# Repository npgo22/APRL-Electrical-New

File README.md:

# APRL KiCad Projects

APRL KiCad Projects.

## Setup
First, clone the repository with `git clone`. GitHub has a button which gives you the command to do this.
Then, you will have to use `git lfs pull` to get all the 3D models and images.

To use the board templates, set `KICAD_USER_TEMPLATE_DIR` by:

1. Going to Preferences > Configure Paths...
2. Setting `KICAD_USER_TEMPLATE_DIR` to wherever you cloned this repo + `/kicadlibs/templates`

## New ALI (Current Project for FQ2026)

### Design
The exigence of this endeavour is twofold:
1. To test the analog frontend designs of our proposed boards for DPF
2. To replace the confusing and elaborate ALI electronics with something that is far better documented and easier to use

The ALI itself can continue to be used for years to come and this reworking of the electronics will not impact it at all. This is going to be its own separate electrical box altogether. The ALI has the following additional limitations, too:
1. Limited I/O
2. Bonded grounds between +24/12/5V power supplies
3. Unknown board-level design decisions/trade-offs made in off-the-shelf components leading to strange artifacts in various measurements
4. Is generally really difficult to understand
5. Mixes bodge-wired custom electronics, off-the-shelf parts, and protoboards
6. Generally has fairly poor mounting
7. Makes use of fairly terrible connectors which are partially damaged and/or have shields which are not properly tied to case GND
8. Is completely full, thus making it impossible to add more electronics
9. Has no methods of cooling, sans the empty hold in the side of the box which completely negate the weather rating of the box itself
10. Uses heterogenous embedded computing ecosystems, requiring cross-domain knowledge of embassy, STM32Cube, and Arduino while doing every single one of them somewhat wrong in one way or another
11. Lacks feedback in many places (error logging namely)
12. Is generally just really hard to work with

Therefore, we have started work on a true replacement. Each of the modules serve a specific task, and are hooked to a common ethernet-based network which is far more performant than the original layout while simultaneously being easier to understand and expand. If you want more I/O, you can just simply add another board within a few minutes. Likewise, by opting for cutouts in the enclosure over dedicated port holes, it is also far easier to revise significant parts of the design without needing to drill through steel. 

#### Power
This system is +5V and +24V only, with +3.3V regulated on each board.

### CANBUS vs Ethernet
On the ground station, we are planning to use Ethernet instead of CANBUS. While this means our session protocol will not be tested in a real-world hotfire scenario, it does mean we can fully exploit each of the features offered by ethernet:
- Higher bandwidth (upwards of ~50x) means we don't have to throttle anything including error logging
- Natural isolation means we don't need any special tricks to get grounded thermocouples to work
- Is just generally far more pleasant to work with
- Does not limit future design decisions should we decide to reuse anything

Each of the modules will have a CAN transceiver anyway available for testing.

## Repository layout

```
kicadlibs/                                 Shared KiCad libraries
  aprl/                                      APRL's custom symbols and footprints
  aprl/*-noct.pretty                         "aprl/" but without courtyards
  vendor/                                    Third-party libs
  models/                                    3D models KiCad does not ship
  APRL_*_Sheet.kicad_wks                     Drawing sheets
  jlcpcb-4layer.kicad_dru                    Canonical JLCPCB design rules
.github/scripts                              Helper scripts runnable via Just and GH actions

ali/2/                                     New ALI electronics
ali/1/                                     Old ALI electronics
ophio/                                     DPF Vehicle Boards
misc/                                      Other endeavors
```

## What's not in this repo
- Old code (incl thermocouple 1A's CubeMX and Embassy variants)
- Prototypes (pending ordering)
- ALI ADC hardware (pending import)

## AI Usage
You may use AI to research topics and to write one-off scripts which do minor modifications and automate tedious, minor tasks. For example, if you need to color in a bunch of models feel free to.

What you *cannot* use it for is end to end electrical design, layout, and documentation. Documents should be written by people, and a schematic falls under this category. Likewise, using AI to automate layout is A. ineffective because it does not generate high-quality layouts and B. defeats the purpose of this club, which is to learn about electronics.

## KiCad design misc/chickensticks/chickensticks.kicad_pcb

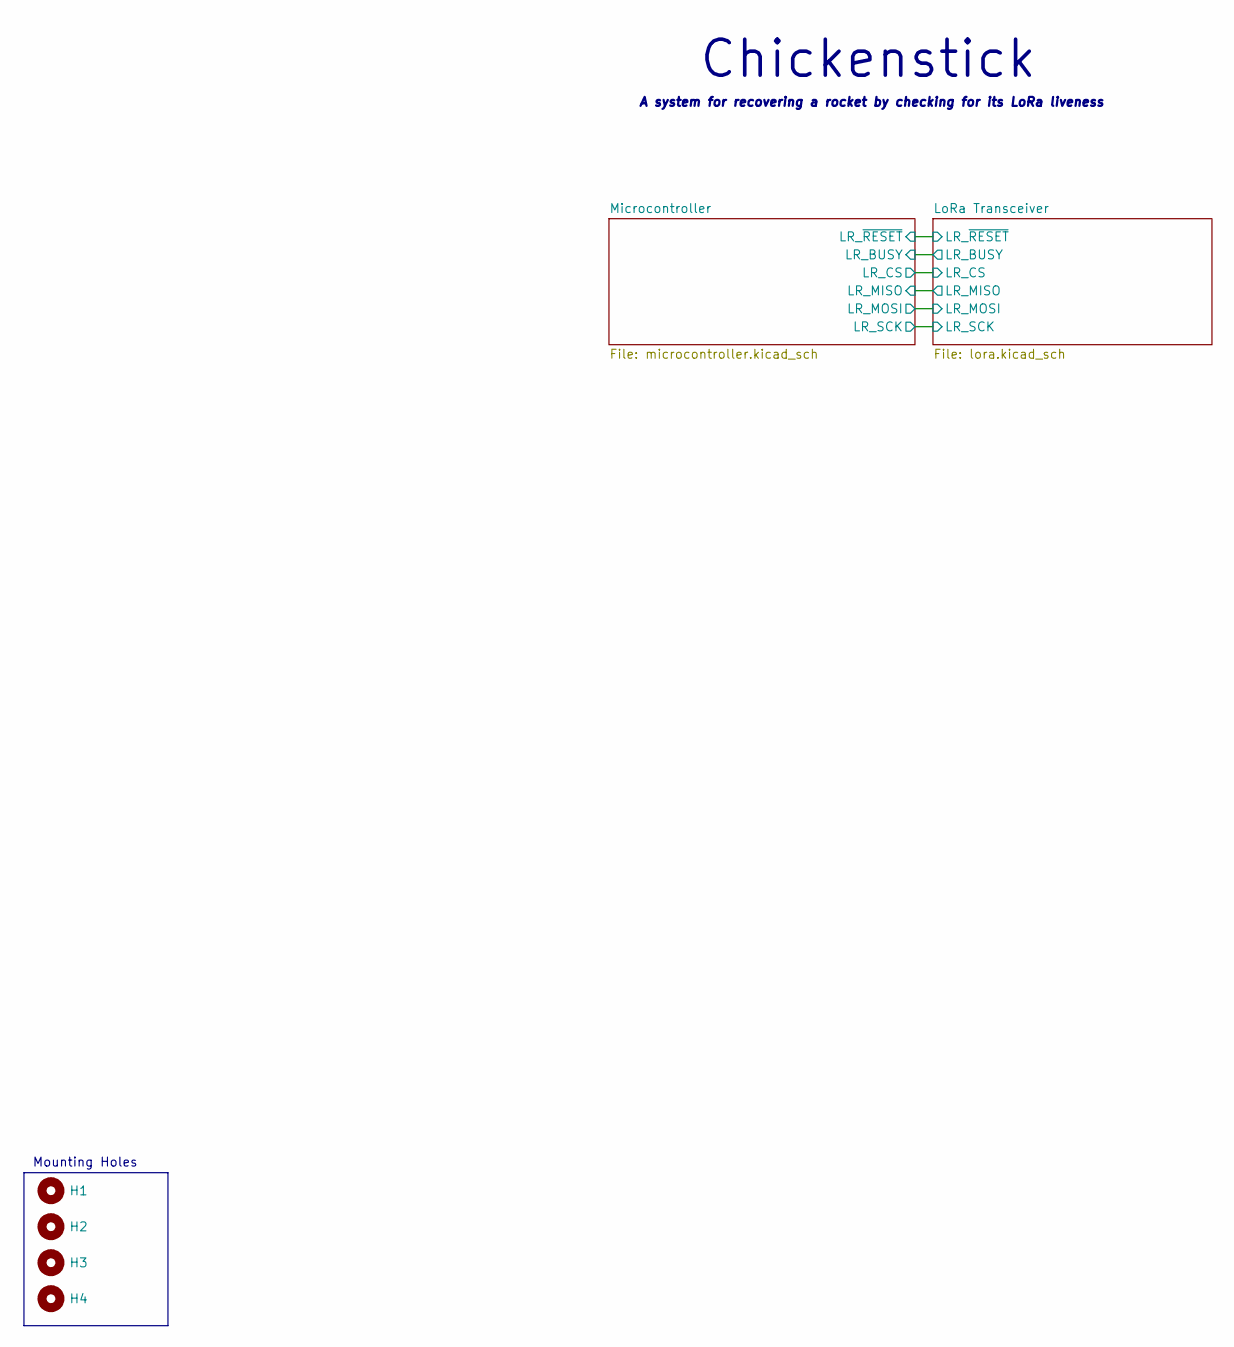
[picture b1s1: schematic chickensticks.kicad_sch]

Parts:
H1, H2, H3, H4: MountingHole; MountingHole_3.2mm_M3

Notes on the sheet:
Chickenstick
A system for recovering a rocket by checking for its LoRa liveness
Mounting Holes

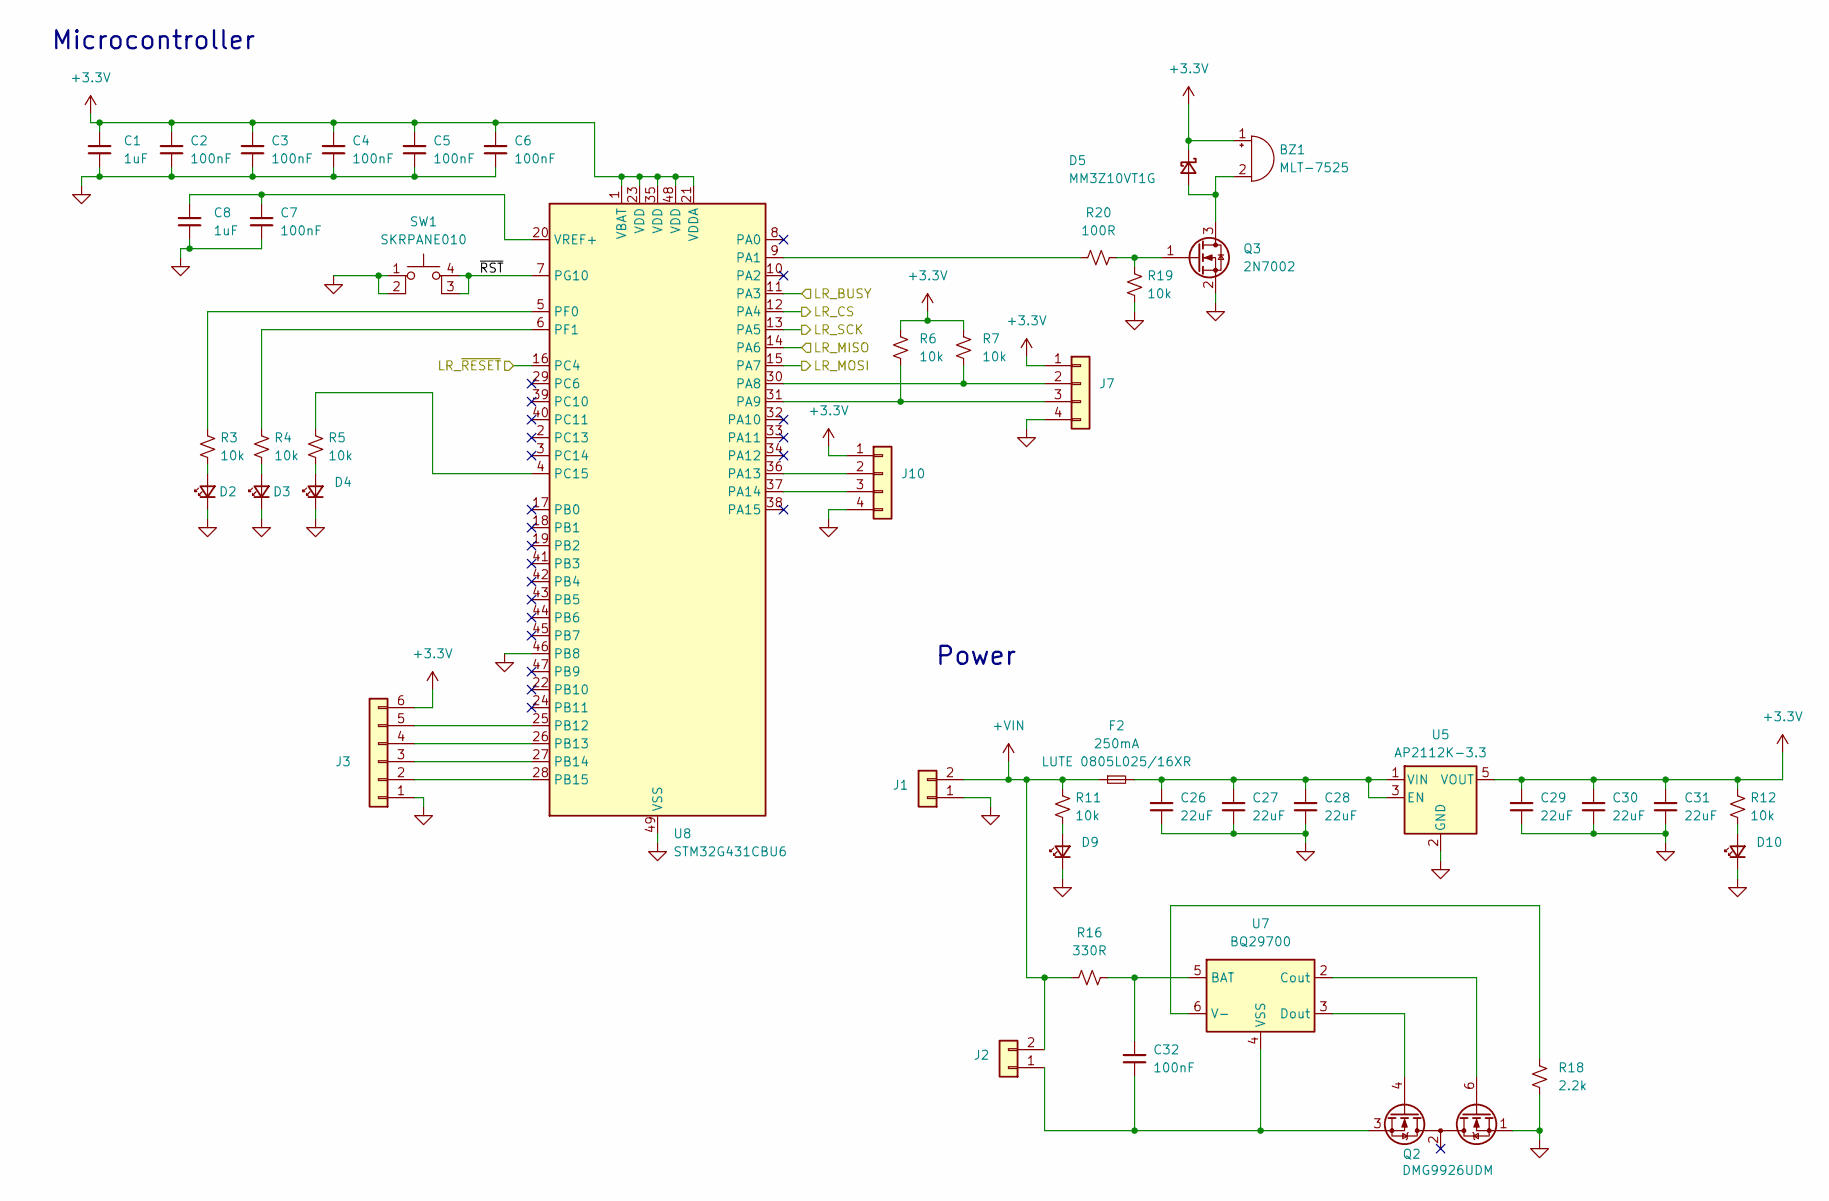
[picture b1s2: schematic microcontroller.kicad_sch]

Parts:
BZ1: MLT-7525
C1, C8: 1uF; C_0805
C2, C3, C4, C5, C6, C7, C32: 100nF; C_0603
C26, C27, C28, C29, C30, C31: 22uF; C_0805
D2, D3, D4, D9, D10: LED_Small; LED_0603
D5: MM3Z10VT1G; SOD-323
F2: 250mA; Fuse_0805_2012Metric
J1, J2: Conn_01x02; Molex_KK-254_AE-6410-02A_1x02_P2.54mm_Vertical
J3: Conn_01x06; Molex_KK-254_AE-6410-06A_1x06_P2.54mm_Vertical
J7, J10: Conn_01x04; PinHeader_1x04_P2.54mm_Vertical
Q2: DMG9926UDM; SOT-23-6
Q3: 2N7002; SOT-23
R3, R4, R5, R6, R7, R11, R12, R19: 10k; R_0603
R16: 330R; R_0603
R18: 2.2k; R_0603
R20: 100R; R_0603
SW1: SKRPANE010
U5: AP2112K-3.3; SOT-23-5
U7: BQ29700; WSON-6_1.5x1.5mm_P0.5mm
U8: STM32G431CBU6; QFN-48_EP_7.3x7.3_Pitch0.5mm

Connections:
+3.3V: BZ1.1 (+), C1.1, C2.1, C3.1, C4.1, C5.1, C6.1, C29.1, C30.1, C31.1, D5.1 (K), J3.6, J7.1, J10.1, R6.1, R7.1, R12.1, U5.5 (VOUT), U8.1 (VBAT), U8.21 (VDDA), U8.23 (VDD), U8.35 (VDD), U8.48 (VDD); also elsewhere on the board
+VIN: F2.1, J1.2, J2.2, R11.1, R16.1
/LoRa Transceiver/LR_BUSY: U8.11 (PA3); also elsewhere on the board
/LoRa Transceiver/LR_CS: U8.12 (PA4); also elsewhere on the board
/LoRa Transceiver/LR_MISO: U8.14 (PA6); also elsewhere on the board
/LoRa Transceiver/LR_MOSI: U8.15 (PA7); also elsewhere on the board
/LoRa Transceiver/LR_SCK: U8.13 (PA5); also elsewhere on the board
/LoRa Transceiver/LR_~RESET: U8.16 (PC4); also elsewhere on the board
/Microcontroller/~RST: SW1.3 (K), SW1.4 (A), U8.7 (PG10)
GND: C1.2, C2.2, C3.2, C4.2, C5.2, C6.2, C7.2, C8.2, C26.2, C27.2, C28.2, C29.2, C30.2, C31.2, D2.1 (K), D3.1 (K), D4.1 (K), D9.1 (K), D10.1 (K), J1.1, J3.1, J7.4, J10.4, Q2.1 (D1), Q3.2 (S), R18.2, R19.2, SW1.1, SW1.2, U5.2 (GND), U8.46 (PB8), U8.49 (VSS); also elsewhere on the board
unnamed: BZ1.2 (-), D5.2 (A), Q3.3 (D)
unnamed: D2.2 (A), R3.2
unnamed: D3.2 (A), R4.2
unnamed: D4.2 (A), R5.2
unnamed: D9.2 (A), R11.2
unnamed: D10.2 (A), R12.2
unnamed: C32.2, J2.1, Q2.3 (S2), U7.4 (VSS)
unnamed: J3.2, U8.28 (PB15)
unnamed: J3.3, U8.27 (PB14)
unnamed: J3.4, U8.26 (PB13)
unnamed: J3.5, U8.25 (PB12)
unnamed: J7.2, R7.2, U8.30 (PA8)
unnamed: J7.3, R6.2, U8.31 (PA9)
unnamed: J10.2, U8.36 (PA13)
unnamed: J10.3, U8.37 (PA14)
unnamed: Q2.6 (G1), U7.2 (Cout)
unnamed: Q2.4 (G2), U7.3 (Dout)
unnamed: Q3.1 (G), R19.1, R20.2
unnamed: C26.1, C27.1, C28.1, F2.2, U5.1 (VIN), U5.3 (EN)
unnamed: C32.1, R16.2, U7.5 (BAT)
unnamed: R18.1, U7.6 (V-)
unnamed: R20.1, U8.9 (PA1)
unnamed: R5.1, U8.4 (PC15)
unnamed: R3.1, U8.5 (PF0)
unnamed: R4.1, U8.6 (PF1)
unnamed: C7.1, C8.1, U8.20 (VREF+)

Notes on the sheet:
Microcontroller
Power

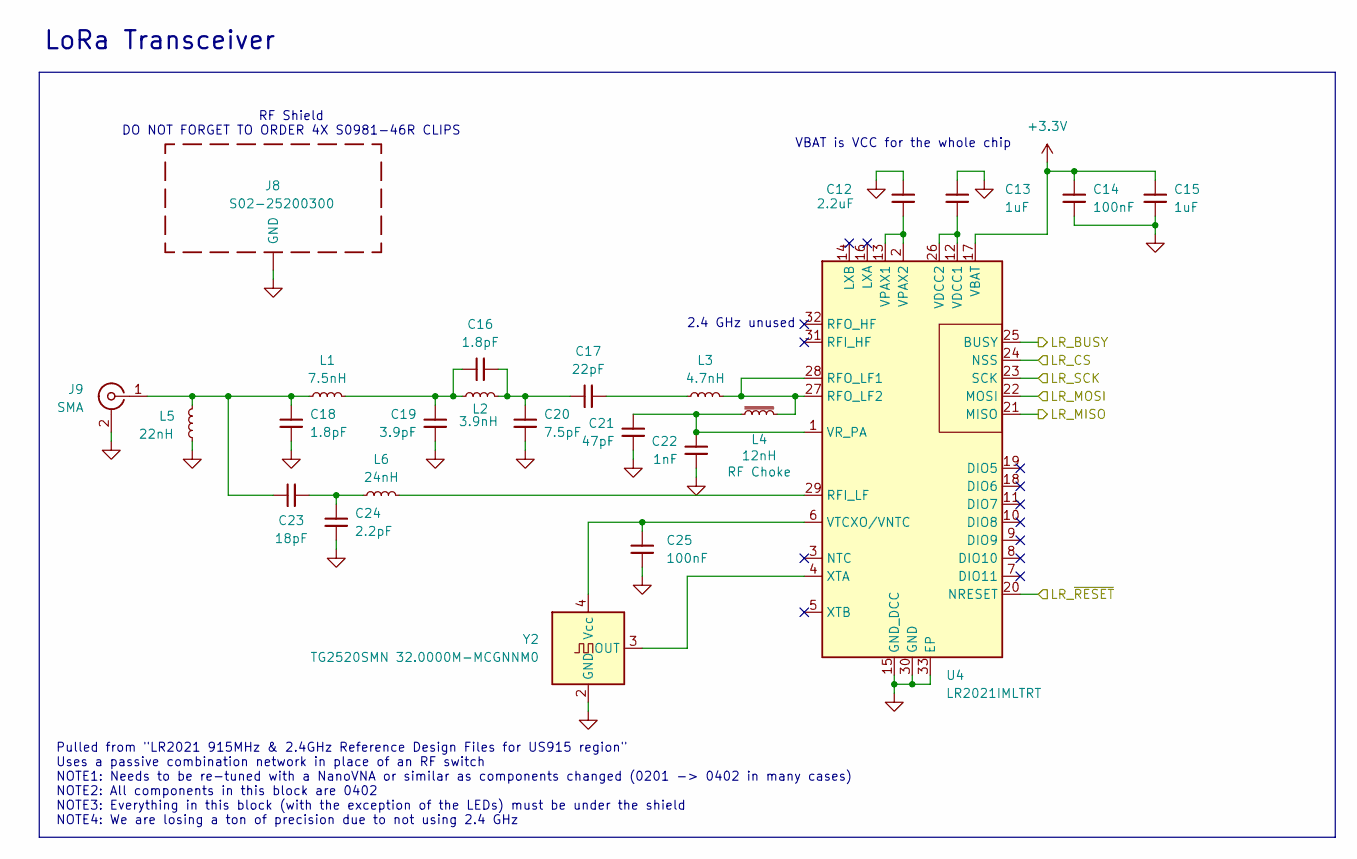
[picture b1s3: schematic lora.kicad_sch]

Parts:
C12: 2.2uF; C_0805
C13, C15: 1uF; C_0805
C14, C25: 100nF; C_0603
C16, C18: 1.8pF; C_0402
C17: 22pF; C_0402
C19: 3.9pF; C_0402
C20: 7.5pF; C_0402
C21: 47pF; C_0402
C22: 1nF; C_0402
C23: 18pF; C_0402
C24: 2.2pF; C_0402
J8: S02-25200300; S02-25200300-Outline
J9: SMA; SMA_Amphenol_132203-12_Horizontal
L1: 7.5nH; L_0402
L2: 3.9nH; L_0402
L3: 4.7nH; L_0402
L4: 12nH; L_0402
L5: 22nH; L_0402
L6: 24nH; L_0402
U4: LR2021IMLTRT; QFN-32_EP_5.8x5.8_Pitch0.5mm
Y2: TG2520SMN 32.0000M-MCGNNM0; Oscillator_SMD_SeikoEpson_TG2520SMN-xxx-xxxxxx-4Pin_2.5x2.0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

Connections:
+3.3V: C14.1, C15.1, U4.17 (VBAT); also elsewhere on the board
/LoRa Transceiver/LR_BUSY: U4.25 (BUSY); also elsewhere on the board
/LoRa Transceiver/LR_CS: U4.24 (NSS); also elsewhere on the board
/LoRa Transceiver/LR_MISO: U4.21 (MISO); also elsewhere on the board
/LoRa Transceiver/LR_MOSI: U4.22 (MOSI); also elsewhere on the board
/LoRa Transceiver/LR_SCK: U4.23 (SCK); also elsewhere on the board
/LoRa Transceiver/LR_~RESET: U4.20 (NRESET); also elsewhere on the board
GND: C12.2, C13.1, C14.2, C15.2, C18.1, C19.1, C20.1, C21.1, C22.1, C24.2, C25.2, J8.GND (GND_GND), J9.2 (Ext), L5.1, U4.15 (GND_DCC), U4.30 (GND), U4.33 (EP), Y2.2 (GND); also elsewhere on the board
unnamed: C16.1, C17.2, C20.2, L2.2
unnamed: C16.2, C19.2, L1.2, L2.1
unnamed: C17.1, L3.1
unnamed: C23.2, C24.1, L6.1
unnamed: C18.2, C23.1, J9.1 (In), L1.1, L5.2
unnamed: L6.2, U4.29 (RFI_LF)
unnamed: L3.2, L4.2, U4.27 (RFO_LF2), U4.28 (RFO_LF1)
unnamed: C13.2, U4.12 (VDCC1), U4.26 (VDCC2)
unnamed: C12.1, U4.2 (VPAX2), U4.13 (VPAX1)
unnamed: C21.2, C22.2, L4.1, U4.1 (VR_PA)
unnamed: C25.1, U4.6 (VTCXO/VNTC), Y2.4 (Vcc)
unnamed: U4.4 (XTA), Y2.3 (OUT)

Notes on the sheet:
RF Shield DO NOT FORGET TO ORDER 4X S0981-46R CLIPS
2.4 GHz unused
Pulled from "LR2021 915MHz & 2.4GHz Reference Design Files for US915 region" Uses a passive combination network in place of an RF switch NOTE1: Needs to be re-tuned with a NanoVNA or similar as components changed (0201 -> 0402 in many cases) NOTE2: All components in this block are 0402 NOTE3: Every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
VBAT is VCC for the whole chip
LoRa Transceiver

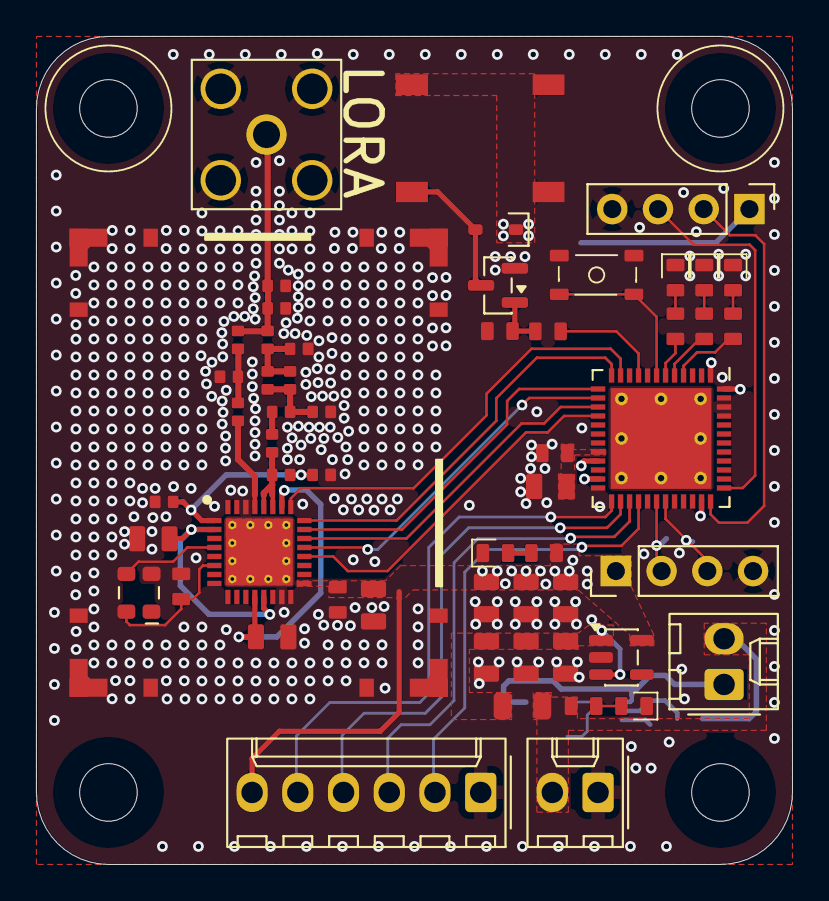
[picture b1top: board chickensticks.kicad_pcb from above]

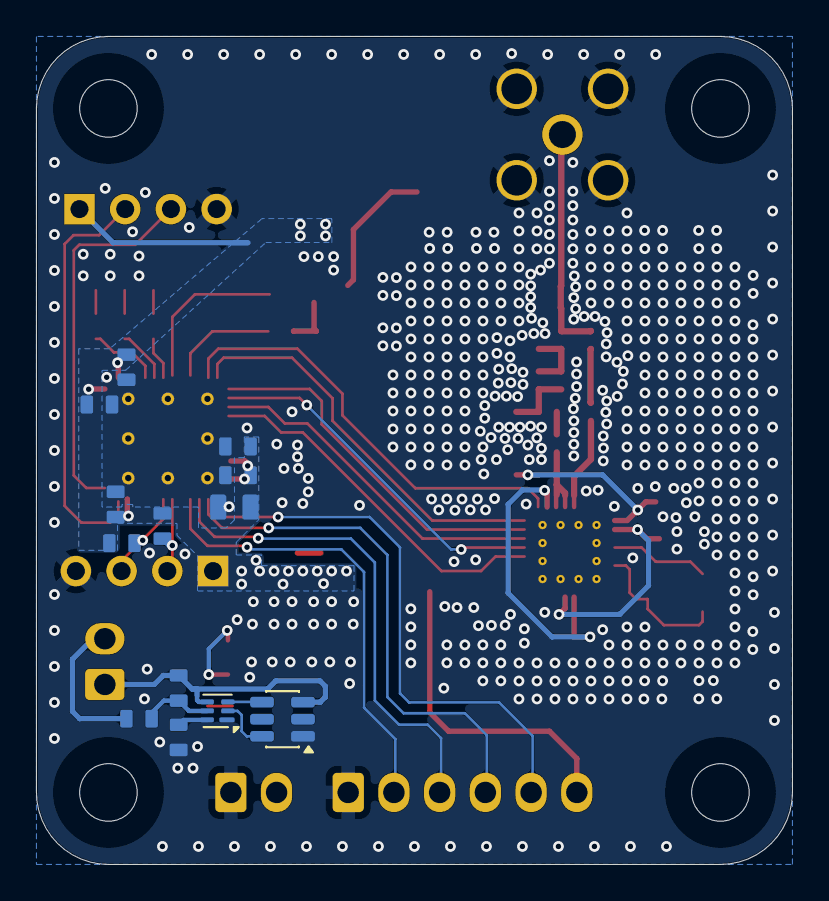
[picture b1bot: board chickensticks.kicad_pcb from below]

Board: 4 copper layers, 42.0 x 46.0 mm, 73 parts (13 on the bottom side), 48 nets.

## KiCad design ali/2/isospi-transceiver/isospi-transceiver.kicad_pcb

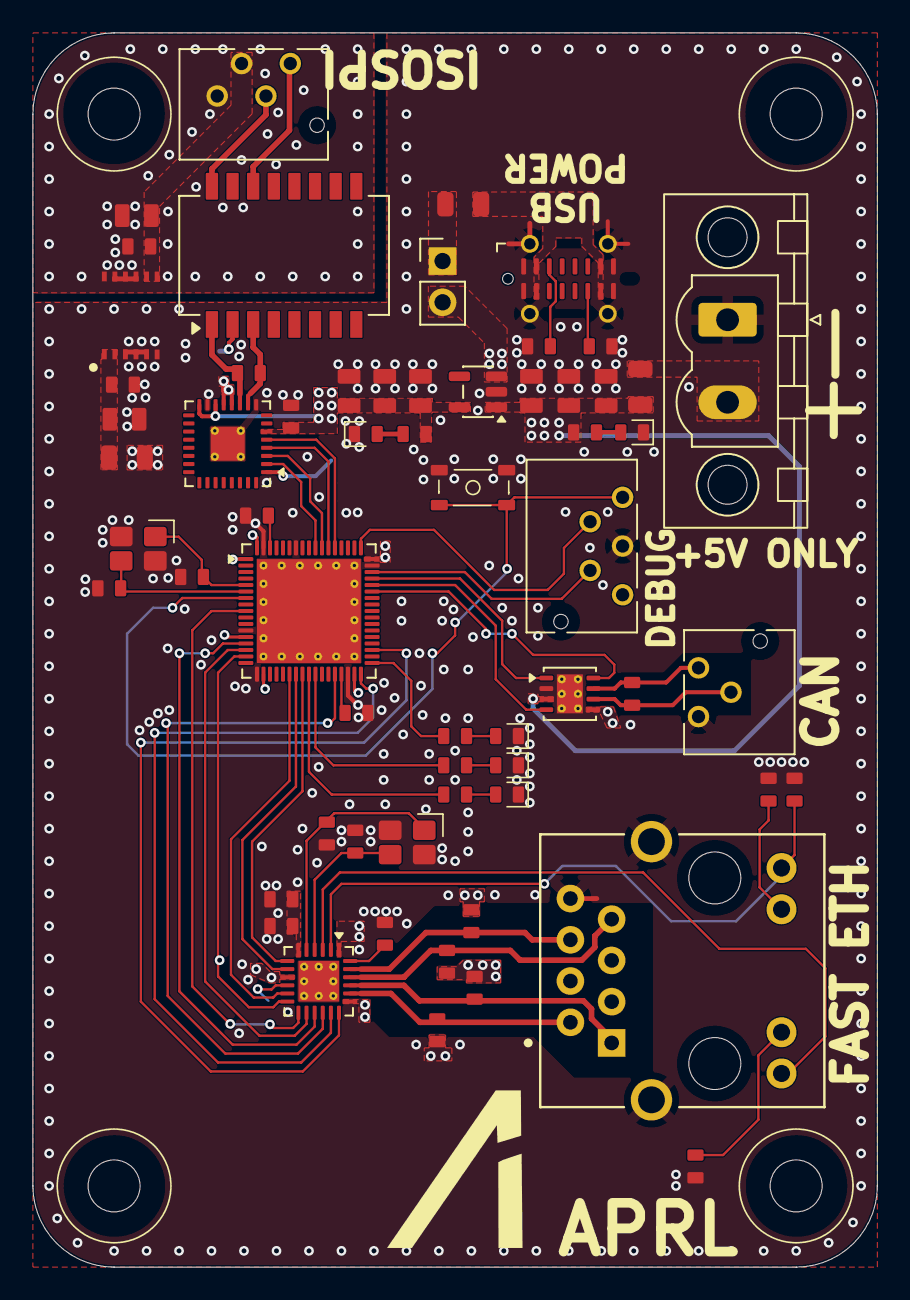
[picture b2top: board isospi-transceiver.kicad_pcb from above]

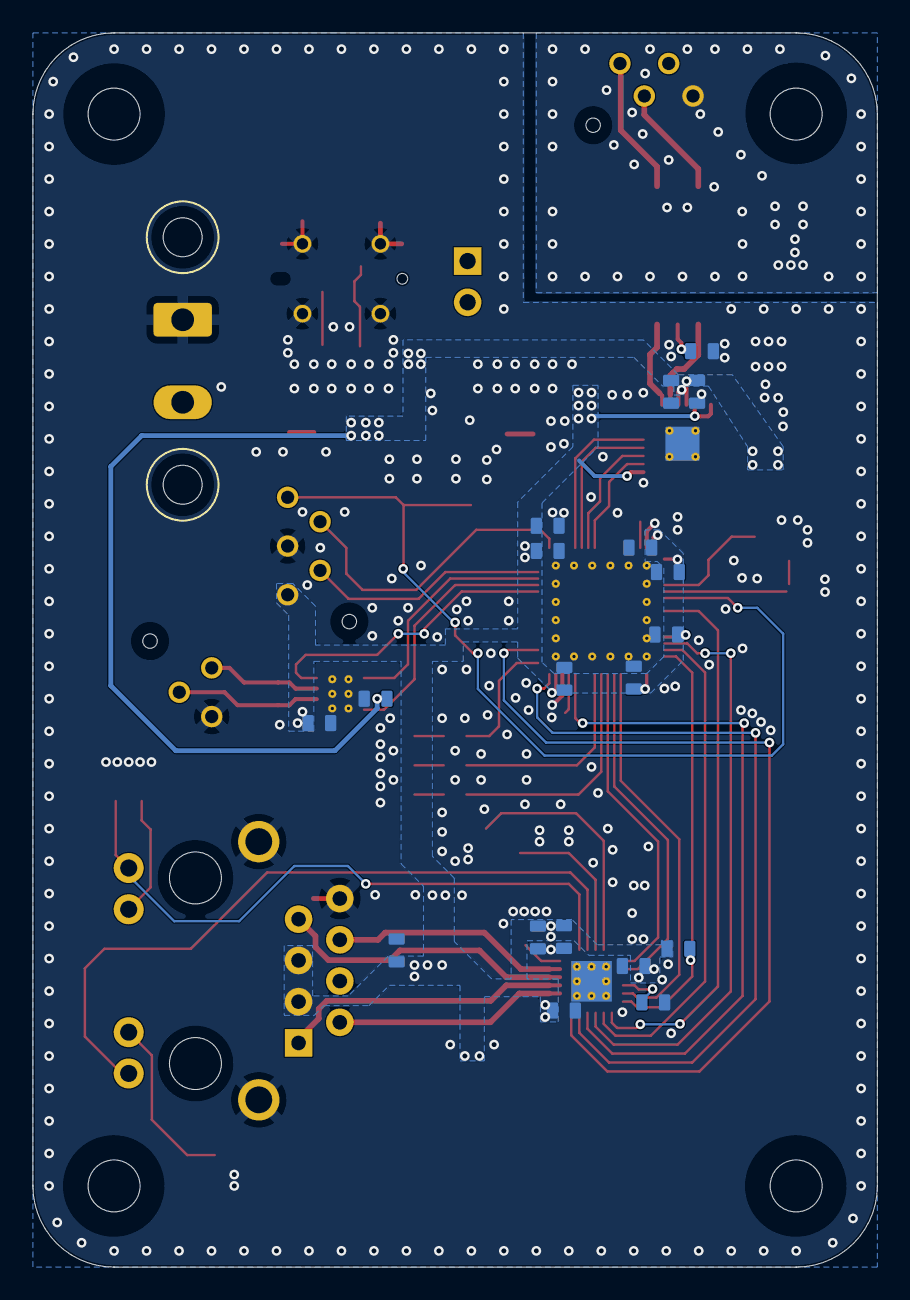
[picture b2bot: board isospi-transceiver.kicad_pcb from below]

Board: 4 copper layers, 52.0 x 76.0 mm, 84 parts (19 on the bottom side), 63 nets.

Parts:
C1, C18, C22: 1uF; C_0603
C2, C3, C4, C5, C6, C7, C19, C20, C21, C27, C28, C29, C30, C31: 100nF; C_0603
C8, C9, C25, C26: 15pF; C_0603
C10, C11: 2.2uF; C_0603
C12, C13, C14, C15, C16, C17, C33, C36: 22uF; C_0805
C23: 470pF; C_0603
C24: 220nF; C_0603
C32, C34, C35: 10nF; C_0603
D1, D2, D3, D4, D5: LED; LED_0603
F1, F2, F3: 500mA; Fuse_0805_2012Metric
H1, H2, H3, H4: MountingHole; MountingHole_3.2mm_M3
J1: Conn_02x01; PinHeader_1x02_P2.54mm_Vertical
J2: Conn_01x05; Molex_CLIK-Mate_503159-0501_1x05-1MP_P1.50mm_Vertical
J3: USB_C_Receptacle_USB2.0_16P; USB_C_Receptacle_G-Switch_GT-USB-7051x
J4: Screw_Terminal_01x02; PhoenixContact_MSTBV_2,5_2-GF-5,08_1x02_P5.08mm_Vertical_Th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
J5: Vertical Ethernet; RJ45_Hanrun_HY951180A_Vertical
J6: Conn_01x03; Molex_CLIK-Mate_503159-0301_1x03-1MP_P1.50mm_Vertical
J7: Conn_01x04; Molex_CLIK-Mate_503159-0401_1x04-1MP_P1.50mm_Vertical
R1, R2: 5.1k; R_0603
R3, R4, R5, R6, R7, R13, R15: 10k; R_0603
R8: 1.5k; R_0603
R9, R10, R11, R12: 47R; R_0603
R14: 12.1k; R_0603
R16, R17: 330R; R_0603
R18: 120R; R_0603
R19: 100R; R_0603
SW1: SKRPANE010
TR1: HX1188NL; Transformer_Ethernet_Pulse_HX1188NL_SO-16_7.11x12.7mm
U1: STM32H563RIV6; QFN-68-1EP_8x8mm_P0.4mm_EP6.4x6.4mm
U2: AP2112K-3.3; SOT-23-5
U3: LAN8742AI; VQFN-24-1EP_4x4mm_P0.5mm_EP2.5x2.5mm_ThermalVias
U4: TJA1462ATK; HVSON-8-1EP_3x3mm_P0.65mm_EP1.6x2.4mm_ThermalVias
U5: ADBMS6821; LFCSP-32-1EP_5x5mm_P0.5mm_EP2.1x2.1mm_ThermalVias
U6: UCC33420-Q1; VSON-12_4x5mm_P0.65mm
Y1, Y2: 25 MHz; 3225-4P-L

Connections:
+3.3V: C1.1, C2.1, C3.1, C4.1, C5.1, C6.1, C7.1, C15.1, C16.1, C17.1, C18.1, C19.1, C20.1, C21.1, C24.1, C28.1, C29.1, J2.1, J5.3 (TCT), J5.5 (RCT), R4.1, R8.1, R9.1, R10.1, R11.1, R12.1, U1.1 (VBAT), U1.13 (VDDA), U1.19 (VDD), U1.33 (VDD), U1.51 (VDD), U1.68 (VDD), U2.5 (VOUT), U3.1 (VDD2A), U3.9 (VDDIO), U3.19 (VDD1A), U4.5 (VIO), U5.1 (MSTR), U5.6 (VDDS), U5.14 (PHAPOL), U5.16 (XCVRMD)
+5V: C12.1, C13.1, C14.1, C27.1, C30.1, C31.1, F2.2, F3.1, J1.2, R3.1, U2.1 (VIN), U2.3 (EN), U4.3 (VCC), U5.12 (VDD), U5.13 (VP)
/Connectivity/ETH_CRS_DV: U1.23 (PA7), U3.11 (CRS_DV/MODE2)
/Connectivity/ETH_MDC: U1.9 (PC1), U3.13 (MDC)
/Connectivity/ETH_MDIO: R8.2, U1.16 (PA2), U3.12 (MDIO)
/Connectivity/ETH_REF_CLK: U1.15 (PA1), U3.14 (~INT/REFCLKO)
/Connectivity/ETH_RXD0: U1.24 (PC4), U3.8 (RXD0/MODE0)
/Connectivity/ETH_RXD1: U1.25 (PC5), U3.7 (RXD1/MODE1)
/Connectivity/ETH_TXD0: U1.34 (PB12), U3.17 (TXD0)
/Connectivity/ETH_TXD1: U1.37 (PB15), U3.18 (TXD1)
/Connectivity/ETH_TX_EN: U1.30 (PB11), U3.16 (TXEN)
/Connectivity/ETH_~RST: U1.14 (PA0), U3.15 (~RST)
/Connectivity/FDCAN_RX: U1.47 (PA11), U4.4 (RXD)
/Connectivity/FDCAN_STDBY: U1.46 (PA10), U4.8 (STB)
/Connectivity/FDCAN_TX: U1.48 (PA12), U4.1 (TXD)
/Microcontroller/MISO: U1.58 (PB4(NJTRST)), U5.3 (POCI)
/Microcontroller/MOSI: U1.59 (PB5), U5.2 (PICO)
/Microcontroller/SCK: U1.57 (PB3(JTDO), U5.4 (SCK)
/Microcontroller/SWCLK: J2.4, U1.52 (PA14(JTCK)
/Microcontroller/SWDIO: J2.2, U1.49 (PA13(JTMS)
/Microcontroller/USER_LED_1: R5.2, U1.26 (PB0)
/Microcontroller/USER_LED_2: R6.2, U1.27 (PB1)
/Microcontroller/USER_LED_3: R7.2, U1.35 (PB13)
/Microcontroller/~CS: U1.56 (PC12), U5.5 (~CS)
/Microcontroller/~RST: J2.5, SW1.3 (K), SW1.4 (A), U1.7 (NRST)
GND: C1.2, C2.2, C3.2, C4.2, C5.2, C6.2, C7.2, C8.2, C9.2, C10.2, C11.2, C12.2, C13.2, C14.2, C15.2, C16.2, C17.2, C18.2, C19.2, C20.2, C21.2, C22.2, C23.2, C24.2, C25.2, C26.2, C27.2, C28.2, C29.2, C30.2, C31.2, C32.1, C33.2, C34.1, D1.1 (K), D2.1 (K), D3.1 (K), D4.1 (K), D5.1 (K), J2.3, J3.A1 (GND), J3.A12 (GND), J3.B1 (GND), J3.B12 (GND), J3.SH (SHIELD), J4.1, J5.8, J5.13, J5.14, J6.3, R1.1, R2.2, R13.1, R14.2, R15.2, R16.2, R17.2, SW1.1, SW1.2, U1.12 (VSSA), U1.18 (VSS), U1.32 (VSS), U1.50 (VSS), U1.62 (BOOT0), U1.67 (VSS), U1.69 (VSS), U2.2 (GND), U3.25 (VSS), U4.2 (GND), U4.9 (GND), U5.9 (GND), U5.15 (RTO), U5.33 (GND), U6.3 (GNDP), U6.4 (GNDP), U6.5 (GNDP), U6.6 (GNDP), Y1.2 (G), Y1.4 (G), Y2.2 (G), Y2.4 (G)
GNDPWR: C35.1, C36.2, J7.4, U6.9 (GNDS), U6.10 (GNDS), U6.11 (GNDS), U6.12 (GNDS)
unnamed: C10.1, U1.31 (VCAP)
unnamed: C11.1, U1.66 (VCAP)
unnamed: D1.2 (A), R3.2
unnamed: D2.2 (A), R4.2
unnamed: D3.2 (A), R5.1
unnamed: D4.2 (A), R6.1
unnamed: D5.2 (A), R7.1
unnamed: F1.1, J3.A4 (VBUS), J3.A9 (VBUS), J3.B4 (VBUS), J3.B9 (VBUS)
unnamed: F1.2, J1.1
unnamed: J3.A5 (CC1), R2.1
unnamed: J3.B5 (CC2), R1.2
unnamed: F2.1, J4.2
unnamed: J5.10, R16.1
unnamed: J5.11, R17.1
unnamed: J5.6 (RD+), R11.2, U3.23 (RXP)
unnamed: J5.7 (RD-), R12.2, U3.22 (RXN)
unnamed: J5.1 (TD+), R9.2, U3.21 (TXP)
unnamed: J5.2 (TD-), R10.2, U3.20 (TXN)
unnamed: J6.1, R18.2, U4.7 (CANH)
unnamed: J6.2, R18.1, U4.6 (CANL)
unnamed: J7.1, TR1.14 (TX-)
unnamed: J7.2, TR1.16 (TX+)
unnamed: C35.2, C36.1, J7.3, U6.7 (SEL), U6.8 (VCC)
unnamed: C32.2, TR1.2 (TCT)
unnamed: R19.1, TR1.1 (TD+), U5.11 (IP)
unnamed: R19.2, TR1.3 (TD-), U5.10 (IM)
unnamed: C8.1, U1.5 (PH0), Y1.1
unnamed: C9.1, U1.6 (PH1), Y1.3
unnamed: J5.9, U3.3 (LED1/REGOFF)
unnamed: J5.12, R15.1, U3.2 (LED2/~INTSEL)
unnamed: R14.1, U3.24 (RBIAS)
unnamed: R13.2, U3.10 (RXER/PHYAD0)
unnamed: C22.1, C23.1, U3.6 (VDDCR)
unnamed: C25.1, U3.5 (XTAL1/CLKIN), Y2.1
unnamed: C26.1, U3.4 (XTAL2), Y2.3
unnamed: C33.1, C34.2, F3.2, U6.1 (EN/FLT), U6.2 (VINP)
